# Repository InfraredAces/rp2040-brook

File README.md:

# rp2040-brook-form
An RP2040 powered board with the form factor of a Brook Universal Fightboard footprint

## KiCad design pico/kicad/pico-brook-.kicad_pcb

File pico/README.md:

The board is composed of Raspberry Pi Pico rather than an RP2040 stamp or an RP2040 with baremetal components. 

)

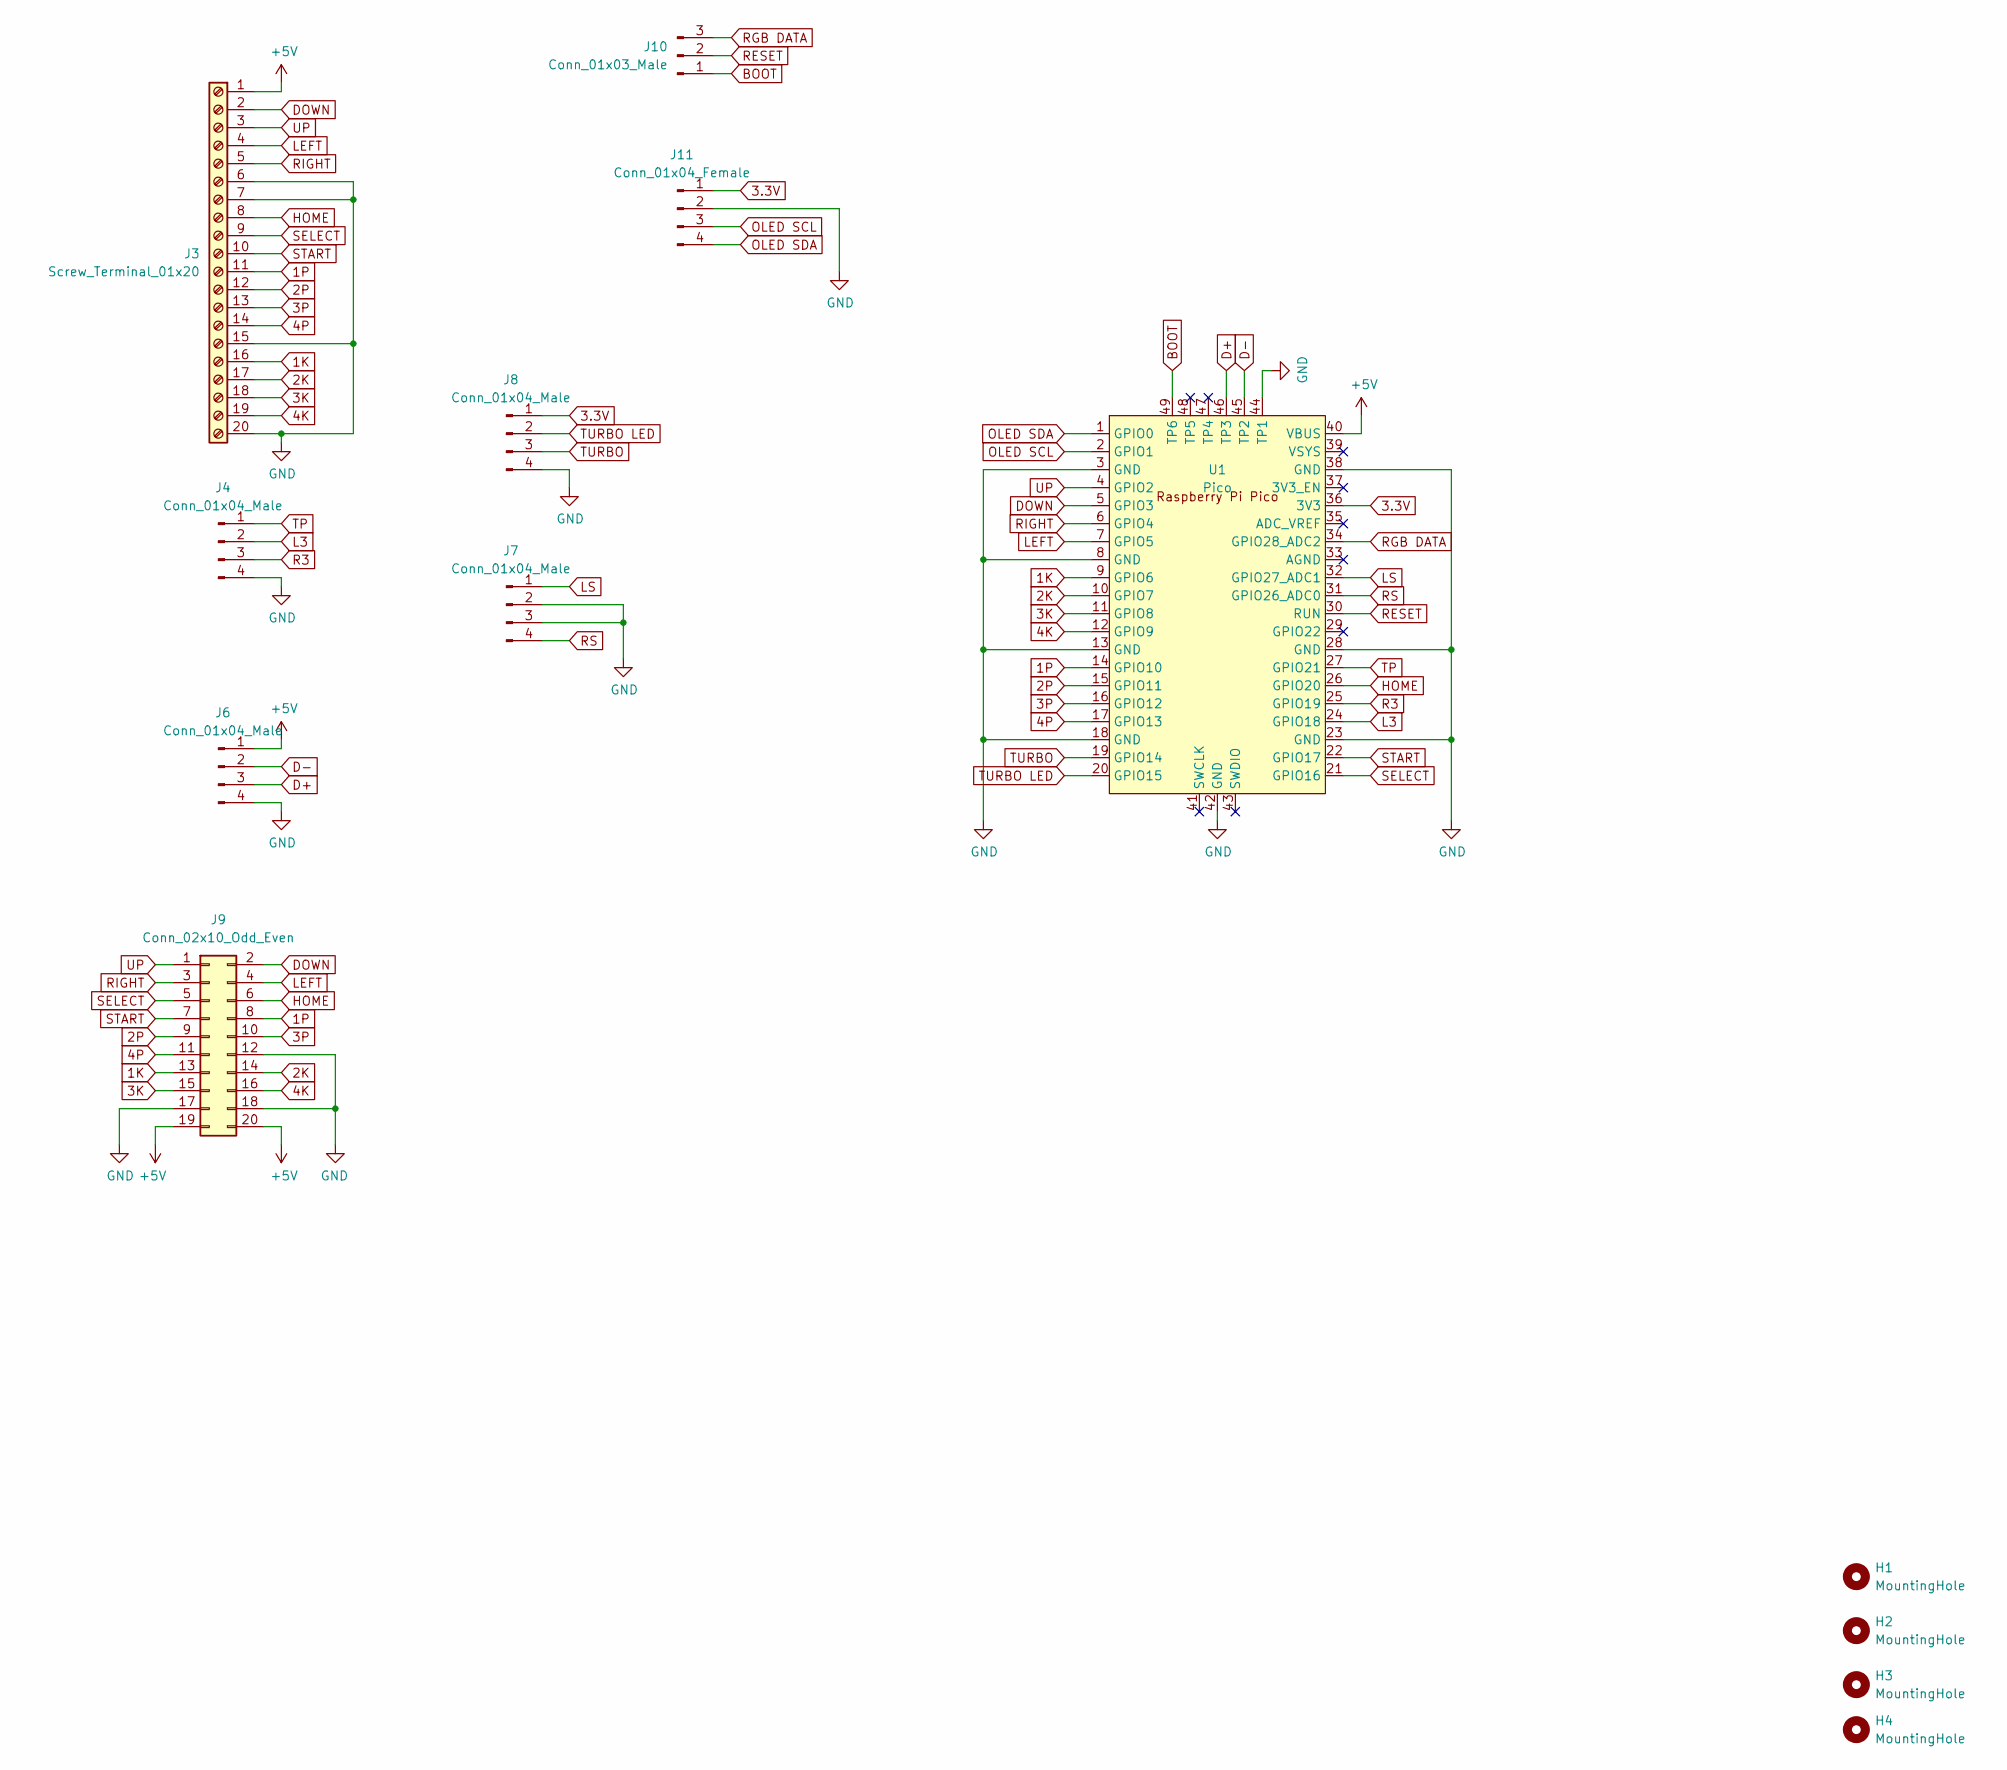
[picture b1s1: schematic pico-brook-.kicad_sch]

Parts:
H1, H2, H3, H4: MountingHole; MountingHole_3.2mm_M3
J3: Screw_Terminal_01x20; Wago_734-150_1x20_P3.50mm_Vertical
J4: Conn_01x04_Male; PinSocket_1x04_P2.00mm_Vertical
J6: Conn_01x04_Male; PinSocket_1x04_P2.54mm_Vertical
J7: Conn_01x04_Male; PinHeader_1x04_P2.54mm_Vertical
J8: Conn_01x04_Male; PinHeader_1x04_P2.00mm_Vertical
J9: Conn_02x10_Odd_Even; PinHeader_2x10_P2.54mm_Vertical
J10: Conn_01x03_Male; PinHeader_1x03_P2.54mm_Vertical
J11: Conn_01x04_Female; PinHeader_1x04_P2.54mm_Vertical
U1: Pico; RPi_Pico_SMD_TH

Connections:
1K: J3.16, J9.13, U1.9 (GPIO6)
1P: J3.11, J9.8, U1.14 (GPIO10)
2K: J3.17, J9.14, U1.10 (GPIO7)
2P: J3.12, J9.9, U1.15 (GPIO11)
3.3V: J8.1, J11.1, U1.36 (3V3)
3K: J3.18, J9.15, U1.11 (GPIO8)
3P: J3.13, J9.10, U1.16 (GPIO12)
4K: J3.19, J9.16, U1.12 (GPIO9)
4P: J3.14, J9.11, U1.17 (GPIO13)
+5V: J3.1, J6.1, J9.19, J9.20, U1.40 (VBUS)
BOOT: J10.1, U1.49 (TP6)
D+: J6.3, U1.46 (TP3)
D-: J6.2, U1.45 (TP2)
DOWN: J3.2, J9.2, U1.5 (GPIO3)
GND: J3.6, J3.7, J3.15, J3.20, J4.4, J6.4, J7.2, J7.3, J8.4, J9.12, J9.17, J9.18, J11.2, U1.3 (GND), U1.8 (GND), U1.13 (GND), U1.18 (GND), U1.23 (GND), U1.28 (GND), U1.38 (GND), U1.42 (GND), U1.44 (TP1)
HOME: J3.8, J9.6, U1.26 (GPIO20)
L3: J4.2, U1.24 (GPIO18)
LEFT: J3.4, J9.4, U1.7 (GPIO5)
LS: J7.1, U1.32 (GPIO27_ADC1)
OLED SCL: J11.3, U1.2 (GPIO1)
OLED SDA: J11.4, U1.1 (GPIO0)
R3: J4.3, U1.25 (GPIO19)
RESET: J10.2, U1.30 (RUN)
RGB DATA: J10.3, U1.34 (GPIO28_ADC2)
RIGHT: J3.5, J9.3, U1.6 (GPIO4)
RS: J7.4, U1.31 (GPIO26_ADC0)
SELECT: J3.9, J9.5, U1.21 (GPIO16)
START: J3.10, J9.7, U1.22 (GPIO17)
TP: J4.1, U1.27 (GPIO21)
TURBO: J8.3, U1.19 (GPIO14)
TURBO LED: J8.2, U1.20 (GPIO15)
UP: J3.3, J9.1, U1.4 (GPIO2)

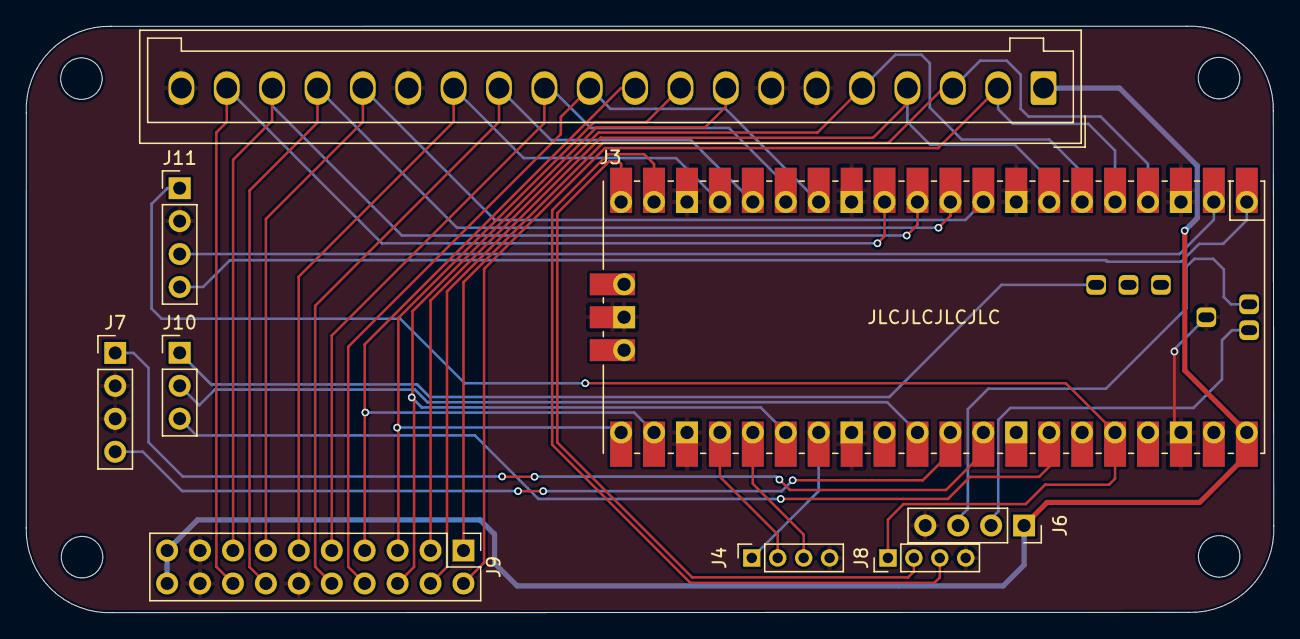
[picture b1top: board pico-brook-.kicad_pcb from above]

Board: 2 copper layers, 96.2 x 45.2 mm, 13 parts (0 on the bottom side), 32 nets.

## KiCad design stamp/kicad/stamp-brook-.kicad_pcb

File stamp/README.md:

The board is composed of an RP2040 stamp rather than a  Raspberry Pi Pico or an RP2040 with baremetal components. 

)

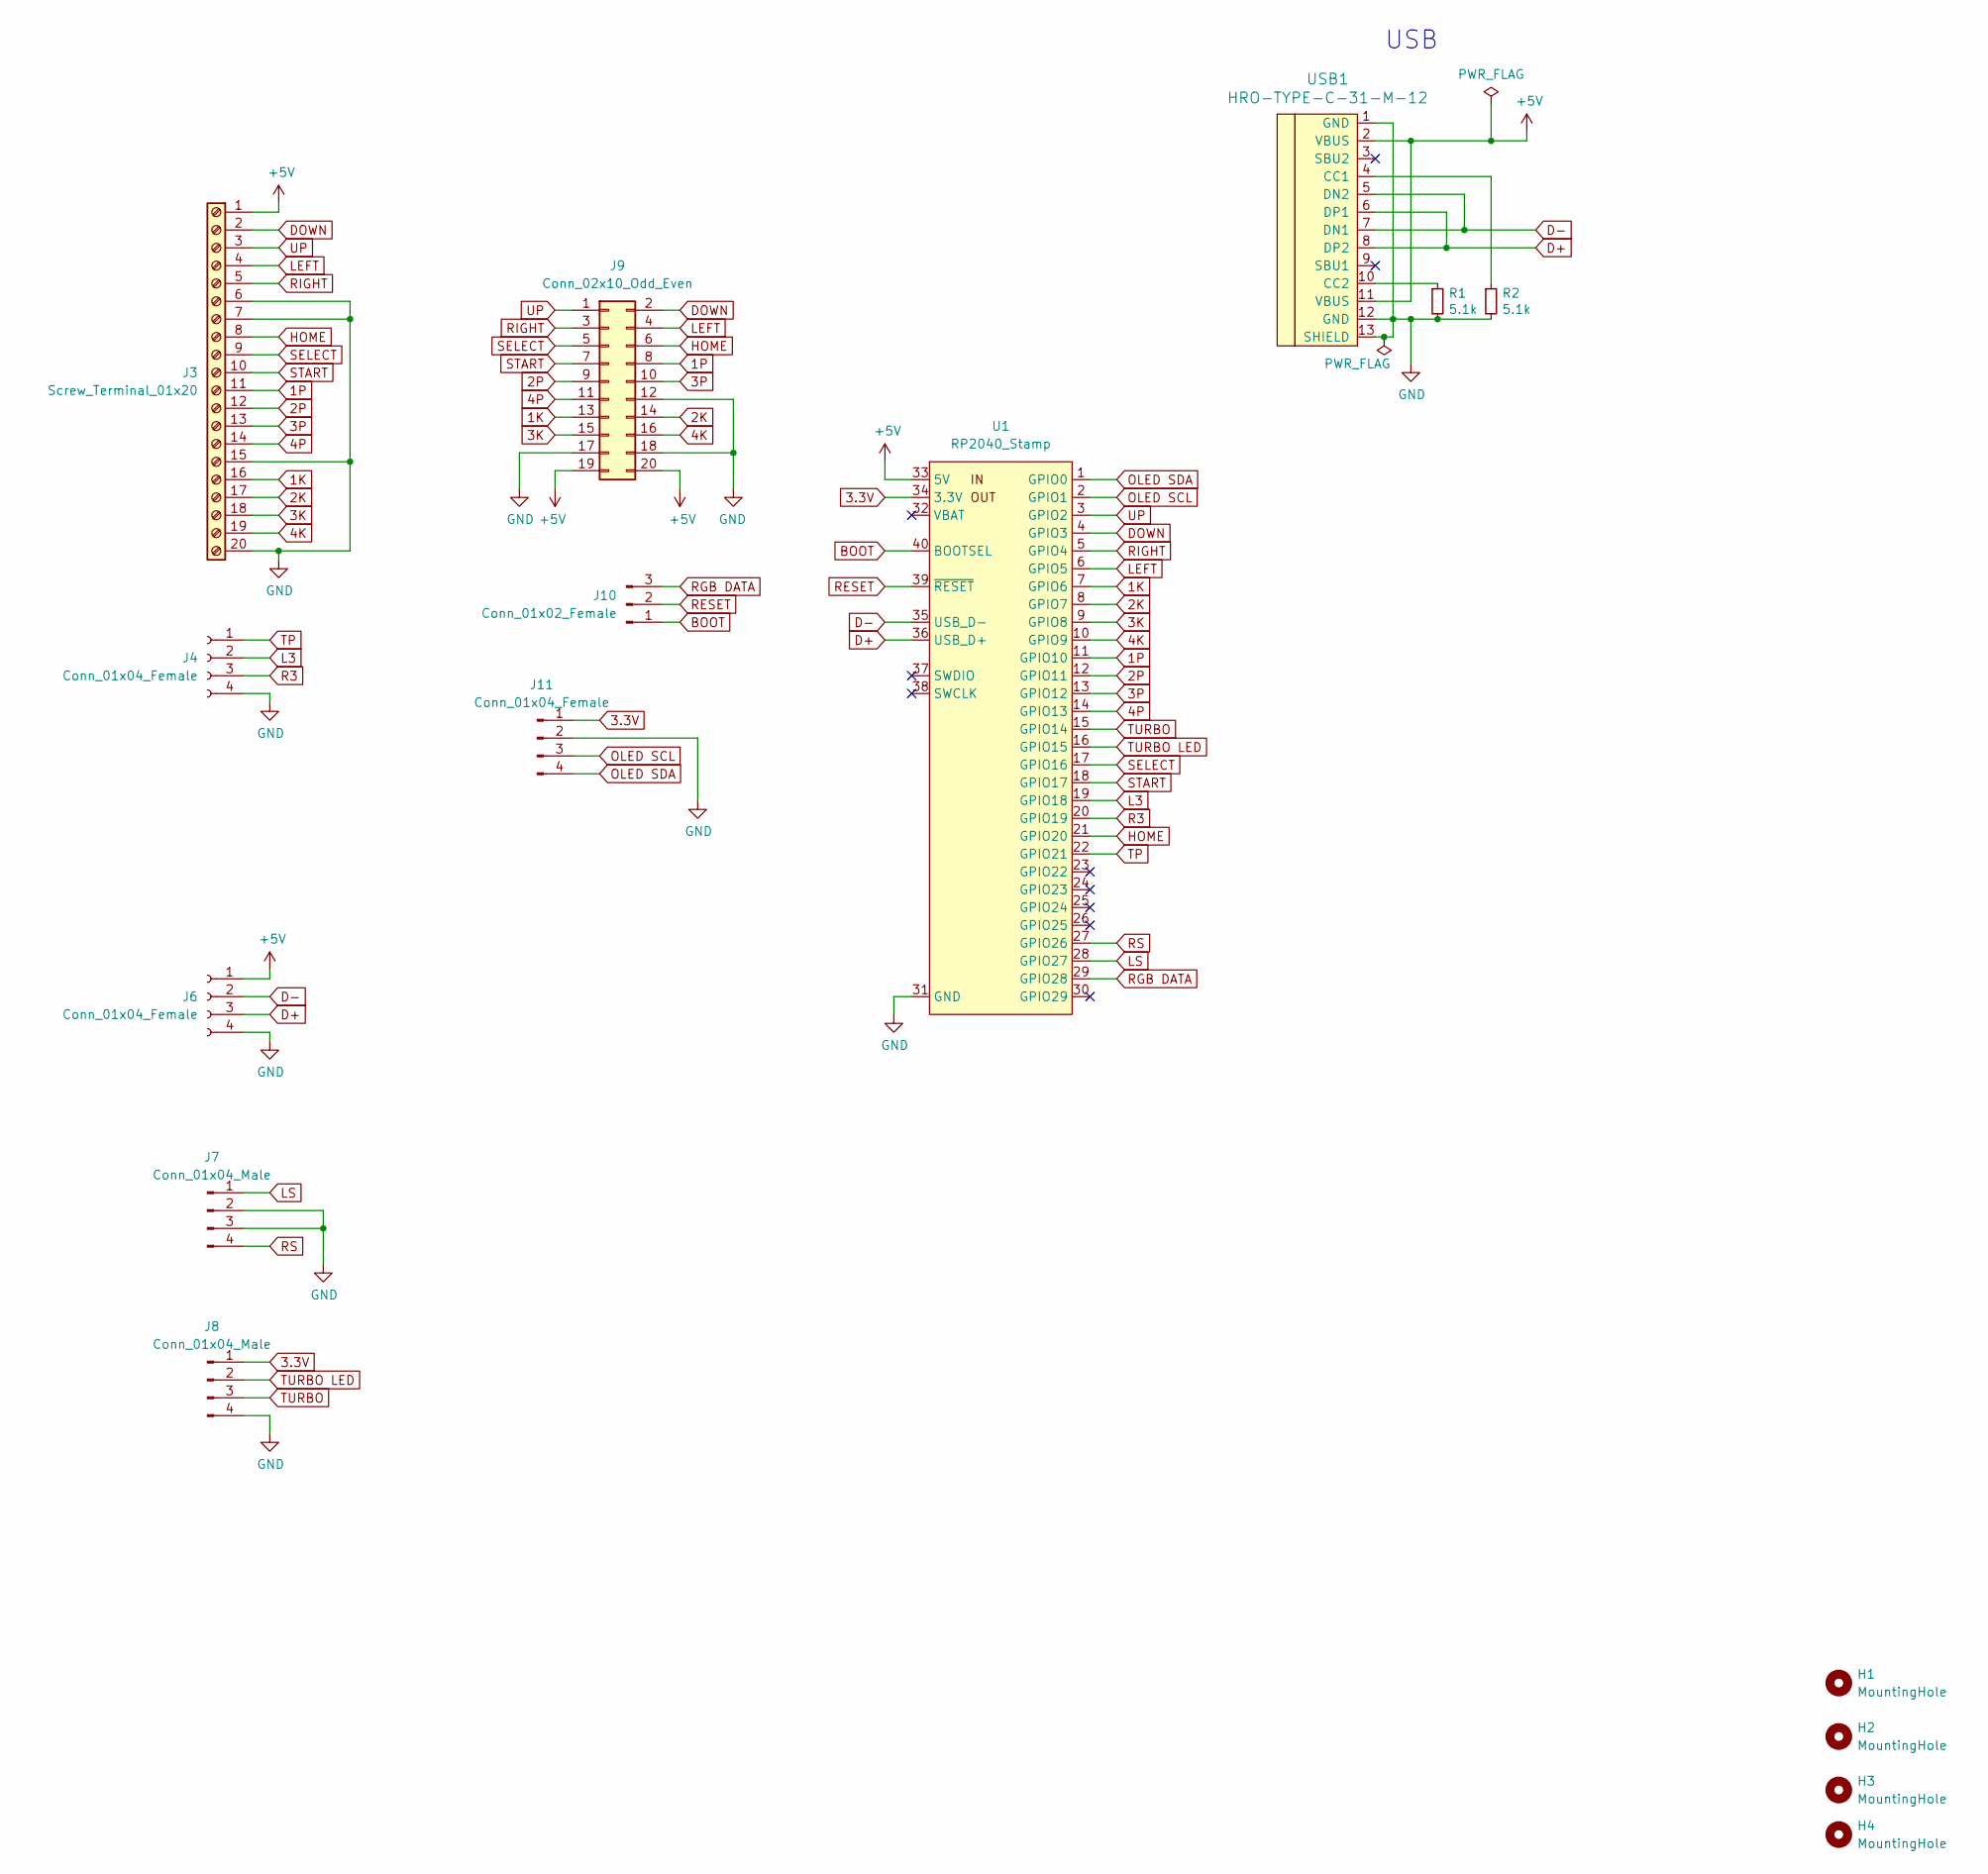
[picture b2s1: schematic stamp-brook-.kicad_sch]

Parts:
H1, H2, H3, H4: MountingHole; MountingHole_3.2mm_M3
J3: Screw_Terminal_01x20; Wago_734-150_1x20_P3.50mm_Vertical
J4: Conn_01x04_Female; PinSocket_1x04_P2.00mm_Vertical
J6: Conn_01x04_Female; PinSocket_1x04_P2.54mm_Vertical
J7: Conn_01x04_Male; PinHeader_1x04_P2.54mm_Vertical
J8: Conn_01x04_Male; PinHeader_1x04_P2.00mm_Vertical
J9: Conn_02x10_Odd_Even; PinSocket_2x10_P2.54mm_Vertical
J10: Conn_01x02_Female; PinHeader_1x03_P2.54mm_Vertical
J11: Conn_01x04_Female; PinHeader_1x04_P2.54mm_Vertical
R1, R2: 5.1k; RESC6332X70N; LCSC C25905
U1: RP2040_Stamp; RP2040_Stamp_SMD
USB1: HRO-TYPE-C-31-M-12; HRO-TYPE-C-31-M-12-Assembly; LCSC C165948

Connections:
1K: J3.16, J9.13, U1.7 (GPIO6)
1P: J3.11, J9.8, U1.11 (GPIO10)
2K: J3.17, J9.14, U1.8 (GPIO7)
2P: J3.12, J9.9, U1.12 (GPIO11)
3.3V: J8.1, J11.1, U1.34 (3.3V)
3K: J3.18, J9.15, U1.9 (GPIO8)
3P: J3.13, J9.10, U1.13 (GPIO12)
4K: J3.19, J9.16, U1.10 (GPIO9)
4P: J3.14, J9.11, U1.14 (GPIO13)
+5V: J3.1, J6.1, J9.19, J9.20, U1.33 (5V), USB1.2 (VBUS), USB1.11 (VBUS)
BOOT: J10.1, U1.40 (BOOTSEL)
D+: J6.3, U1.36 (USB_D+), USB1.6 (DP1), USB1.8 (DP2)
D-: J6.2, U1.35 (USB_D-), USB1.5 (DN2), USB1.7 (DN1)
DOWN: J3.2, J9.2, U1.4 (GPIO3)
GND: J3.6, J3.7, J3.15, J3.20, J4.4, J6.4, J7.2, J7.3, J8.4, J9.12, J9.17, J9.18, J11.2, R1.2, R2.2, U1.31 (GND), USB1.1 (GND), USB1.12 (GND), USB1.13 (SHIELD)
HOME: J3.8, J9.6, U1.21 (GPIO20)
L3: J4.2, U1.19 (GPIO18)
LEFT: J3.4, J9.4, U1.6 (GPIO5)
LS: J7.1, U1.28 (GPIO27)
unnamed: R1.1, USB1.10 (CC2)
unnamed: R2.1, USB1.4 (CC1)
OLED SCL: J11.3, U1.2 (GPIO1)
OLED SDA: J11.4, U1.1 (GPIO0)
R3: J4.3, U1.20 (GPIO19)
RESET: J10.2, U1.39 (~RESET)
RGB DATA: J10.3, U1.29 (GPIO28)
RIGHT: J3.5, J9.3, U1.5 (GPIO4)
RS: J7.4, U1.27 (GPIO26)
SELECT: J3.9, J9.5, U1.17 (GPIO16)
START: J3.10, J9.7, U1.18 (GPIO17)
TP: J4.1, U1.22 (GPIO21)
TURBO: J8.3, U1.15 (GPIO14)
TURBO LED: J8.2, U1.16 (GPIO15)
UP: J3.3, J9.1, U1.3 (GPIO2)

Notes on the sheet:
USB

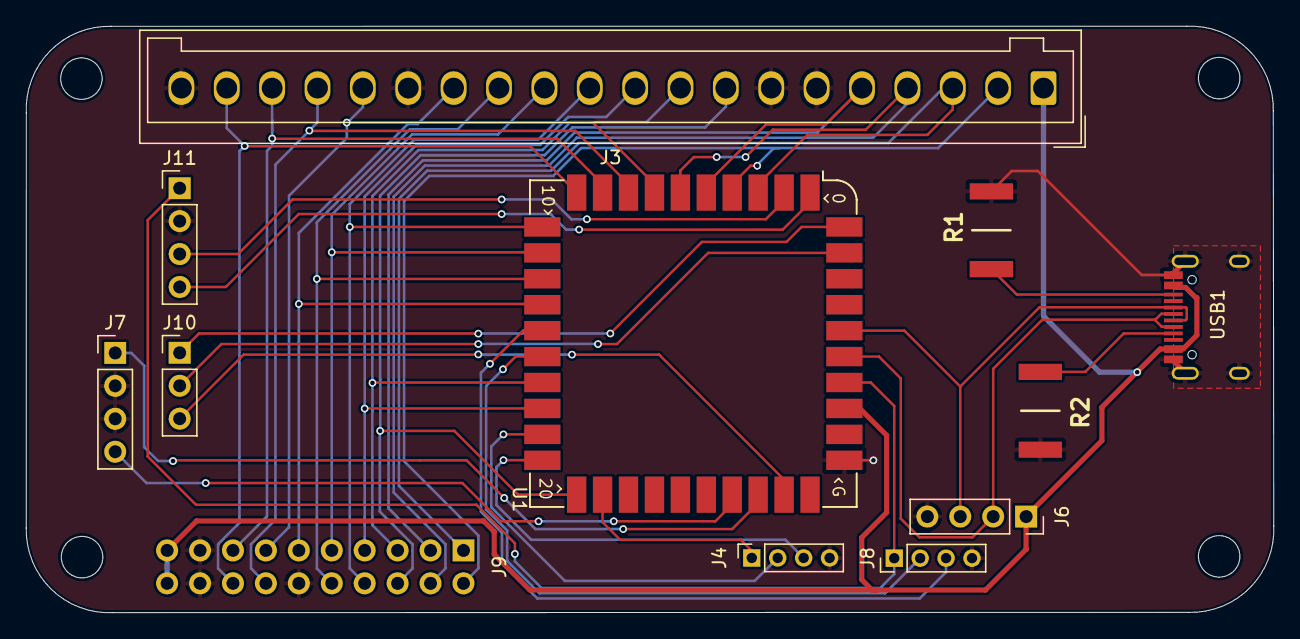
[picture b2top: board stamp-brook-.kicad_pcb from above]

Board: 2 copper layers, 96.2 x 45.2 mm, 16 parts (1 on the bottom side), 34 nets.

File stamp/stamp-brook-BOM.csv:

Comment,Designator,Footprint,LCSC
"MountingHole","H1,H2,H3,H4","MountingHole:MountingHole_3.2mm_M3",""
"Conn_01x02_Female","J10","Connector_PinHeader_2.54mm:PinHeader_1x03_P2.54mm_Vertical",""
"Conn_01x05_Male","J2,J5","Connector_PinHeader_2.00mm:PinHeader_1x05_P2.00mm_Vertical",""
"Screw_Terminal_01x20","J3","Connector_Wago:Wago_734-150_1x20_P3.50mm_Vertical",""
"Conn_01x04_Female","J4","Connector_PinSocket_2.00mm:PinSocket_1x04_P2.00mm_Vertical",""
"Conn_01x04_Female","J6","Connector_PinSocket_2.54mm:PinSocket_1x04_P2.54mm_Vertical",""
"Conn_01x04_Male","J7","Connector_PinHeader_2.54mm:PinHeader_1x04_P2.54mm_Vertical",""
"Conn_01x04_Male","J8","Connector_PinHeader_2.00mm:PinHeader_1x04_P2.00mm_Vertical",""
"Conn_02x10_Odd_Even","J9","Connector_PinSocket_2.54mm:PinSocket_2x10_P2.54mm_Vertical",""
"5.1k","R1,R2","Resistor_SMD:R_0402_1005Metric","C25905"
"RP2040_Stamp","U1","RP2040_Stamp:RP2040_Stamp_SMD",""
"HRO-TYPE-C-31-M-12","USB1","Type-C:HRO-TYPE-C-31-M-12-Assembly","C165948"

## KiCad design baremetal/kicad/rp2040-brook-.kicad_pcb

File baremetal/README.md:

The board is composed of an RP2040 with baremetal components rather than an RP2040 stamp or Raspberry Pi Pico.

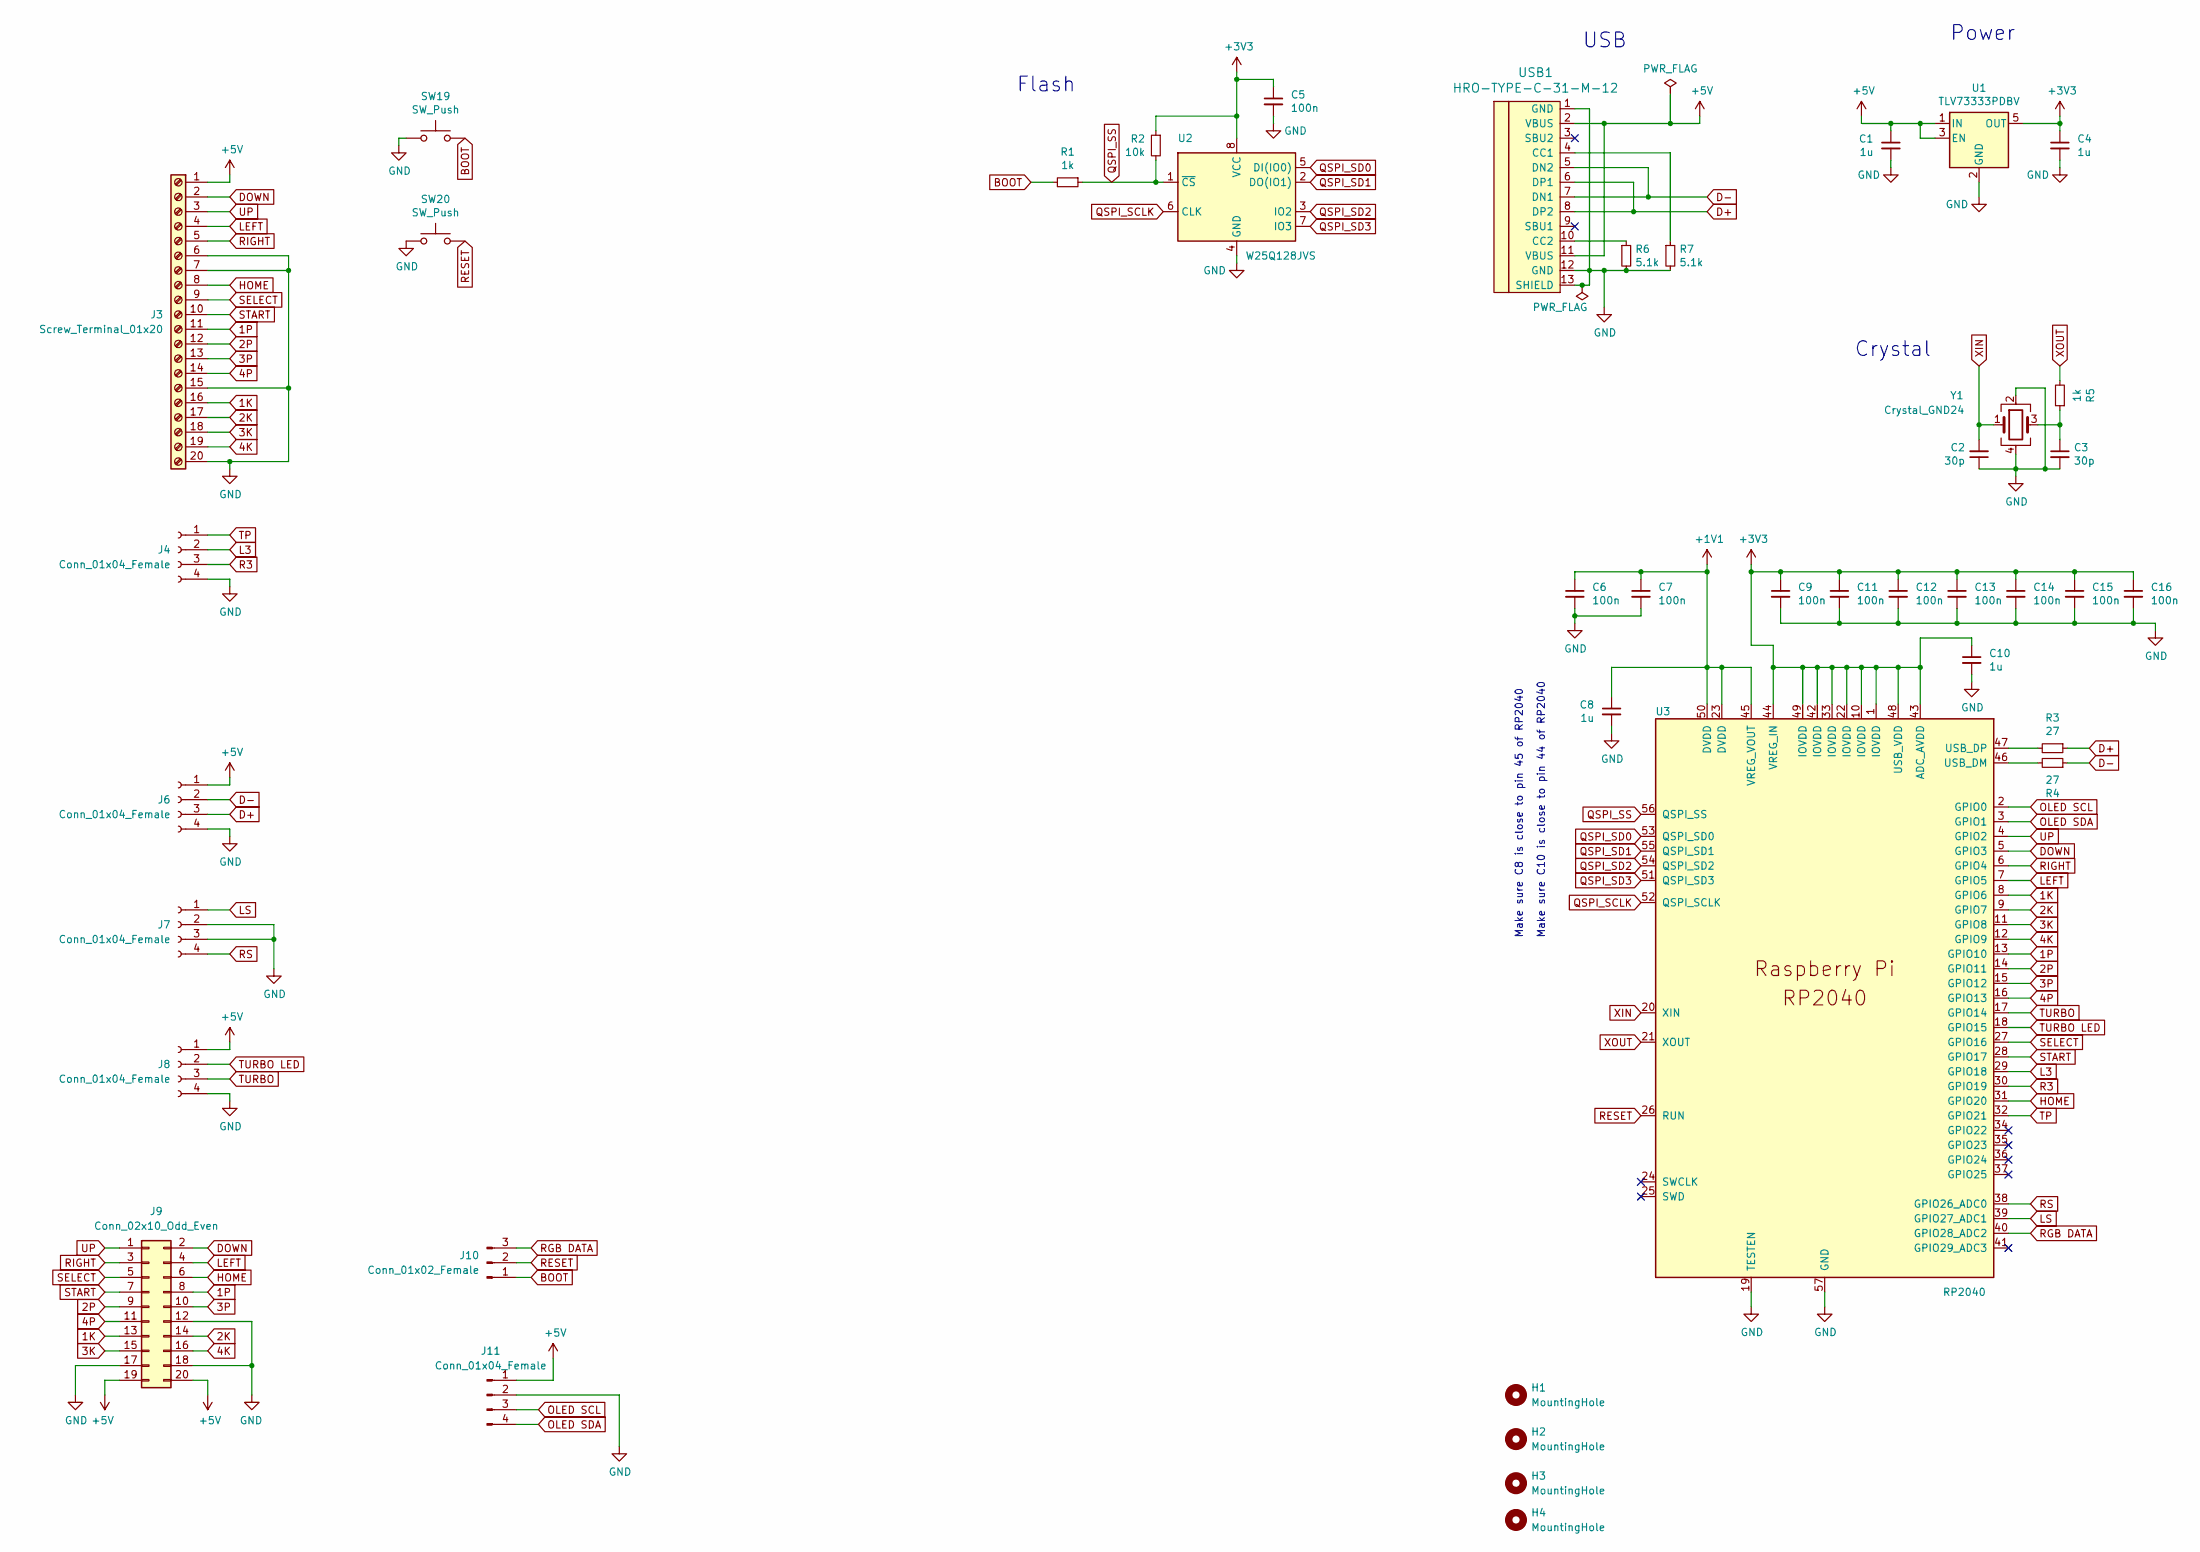
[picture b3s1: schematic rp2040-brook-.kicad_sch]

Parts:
C1, C4, C8, C10: 1u; C_0402_1005Metric; LCSC C52923
C2, C3: 30p; C_0402_1005Metric; LCSC C1570
C5, C6, C7, C9, C11, C12, C13, C14, C15, C16: 100n; C_0402_1005Metric; LCSC C1525
H1, H2, H3, H4: MountingHole; MountingHole_3.2mm_M3
J3: Screw_Terminal_01x20; Wago_734-150_1x20_P3.50mm_Vertical
J4, J8: Conn_01x04_Female; PinSocket_1x04_P2.00mm_Vertical
J6, J7: Conn_01x04_Female; PinSocket_1x04_P2.54mm_Vertical
J9: Conn_02x10_Odd_Even; PinSocket_2x10_P2.54mm_Vertical
J10: Conn_01x02_Female; PinHeader_1x03_P2.54mm_Vertical
J11: Conn_01x04_Female; PinHeader_1x04_P2.54mm_Vertical
R1, R5: 1k; R_0402_1005Metric; LCSC C11702
R2: 10k; R_0402_1005Metric; LCSC C25744
R3, R4: 27; R_0402_1005Metric; LCSC C138021
R6, R7: 5.1k; R_0402_1005Metric; LCSC C25905
SW19, SW20: SW_Push; SW_SPST_Omron_B3FS-100xP; LCSC C271750
U1: TLV73333PDBV; SOT-23-5; LCSC C134139
U2: W25Q128JVS; SOIC-8_5.23x5.23mm_P1.27mm; LCSC C97521
U3: RP2040; RP2040-QFN-56; LCSC C2040
USB1: HRO-TYPE-C-31-M-12; HRO-TYPE-C-31-M-12-Assembly; LCSC C165948
Y1: Crystal_GND24; Crystal_SMD_3225-4Pin_3.2x2.5mm; LCSC C9002

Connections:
1K: J3.16, J9.13, U3.8 (GPIO6)
1P: J3.11, J9.8, U3.13 (GPIO10)
2K: J3.17, J9.14, U3.9 (GPIO7)
2P: J3.12, J9.9, U3.14 (GPIO11)
3K: J3.18, J9.15, U3.11 (GPIO8)
3P: J3.13, J9.10, U3.15 (GPIO12)
4K: J3.19, J9.16, U3.12 (GPIO9)
4P: J3.14, J9.11, U3.16 (GPIO13)
+1V1: C6.1, C7.1, C8.1, U3.23 (DVDD), U3.45 (VREG_VOUT), U3.50 (DVDD)
+3V3: C4.1, C5.1, C9.1, C10.1, C11.1, C12.1, C13.1, C14.1, C15.1, C16.1, R2.1, U1.5 (OUT), U2.8 (VCC), U3.1 (IOVDD), U3.10 (IOVDD), U3.22 (IOVDD), U3.33 (IOVDD), U3.42 (IOVDD), U3.43 (ADC_AVDD), U3.44 (VREG_IN), U3.48 (USB_VDD), U3.49 (IOVDD)
+5V: C1.1, J3.1, J6.1, J8.1, J9.19, J9.20, J11.1, U1.1 (IN), U1.3 (EN), USB1.2 (VBUS), USB1.11 (VBUS)
BOOT: J10.1, R1.2, SW19.2
D+: J6.3, R3.1, USB1.6 (DP1), USB1.8 (DP2)
D-: J6.2, R4.1, USB1.5 (DN2), USB1.7 (DN1)
DOWN: J3.2, J9.2, U3.5 (GPIO3)
GND: C1.2, C2.1, C3.2, C4.2, C5.2, C6.2, C7.2, C8.2, C9.2, C10.2, C11.2, C12.2, C13.2, C14.2, C15.2, C16.2, J3.6, J3.7, J3.15, J3.20, J4.4, J6.4, J7.2, J7.3, J8.4, J9.12, J9.17, J9.18, J11.2, R6.2, R7.2, SW19.1, SW20.1, U1.2 (GND), U2.4 (GND), U3.19 (TESTEN), U3.57 (GND), USB1.1 (GND), USB1.12 (GND), USB1.13 (SHIELD), Y1.2, Y1.4
HOME: J3.8, J9.6, U3.31 (GPIO20)
L3: J4.2, U3.29 (GPIO18)
LEFT: J3.4, J9.4, U3.7 (GPIO5)
LS: J7.1, U3.39 (GPIO27_ADC1)
unnamed: C3.1, R5.1, Y1.3
unnamed: R3.2, U3.47 (USB_DP)
unnamed: R4.2, U3.46 (USB_DM)
unnamed: R6.1, USB1.10 (CC2)
unnamed: R7.1, USB1.4 (CC1)
OLED SCL: J11.3, U3.2 (GPIO0)
OLED SDA: J11.4, U3.3 (GPIO1)
QSPI_SCLK: U2.6 (CLK), U3.52 (QSPI_SCLK)
QSPI_SD0: U2.5 (DI(IO0)), U3.53 (QSPI_SD0)
QSPI_SD1: U2.2 (DO(IO1)), U3.55 (QSPI_SD1)
QSPI_SD2: U2.3 (IO2), U3.54 (QSPI_SD2)
QSPI_SD3: U2.7 (IO3), U3.51 (QSPI_SD3)
QSPI_SS: R1.1, R2.2, U2.1 (~CS), U3.56 (QSPI_SS)
R3: J4.3, U3.30 (GPIO19)
RESET: J10.2, SW20.2, U3.26 (RUN)
RGB DATA: J10.3, U3.40 (GPIO28_ADC2)
RIGHT: J3.5, J9.3, U3.6 (GPIO4)
RS: J7.4, U3.38 (GPIO26_ADC0)
SELECT: J3.9, J9.5, U3.27 (GPIO16)
START: J3.10, J9.7, U3.28 (GPIO17)
TP: J4.1, U3.32 (GPIO21)
TURBO: J8.3, U3.17 (GPIO14)
TURBO LED: J8.2, U3.18 (GPIO15)
UP: J3.3, J9.1, U3.4 (GPIO2)
XIN: C2.2, U3.20 (XIN), Y1.1
XOUT: R5.2, U3.21 (XOUT)

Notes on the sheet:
Make sure C8 is close to pin 45 of RP2040
Make sure C10 is close to pin 44 of RP2040
Power
USB
Flash
Crystal

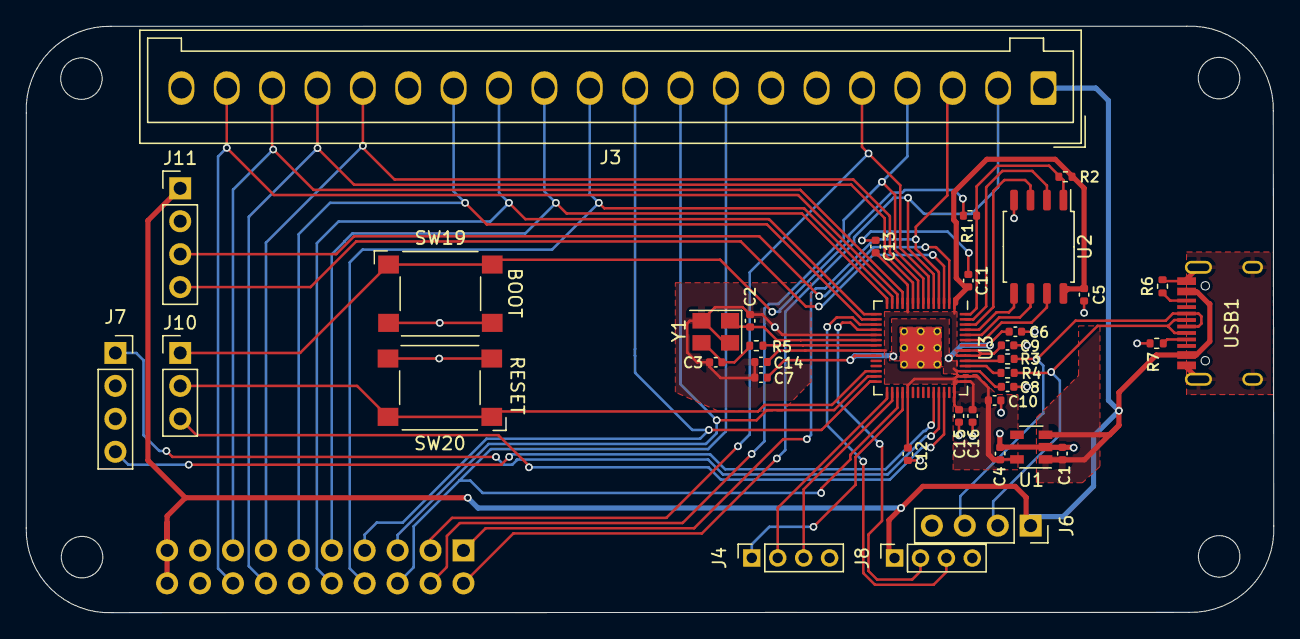
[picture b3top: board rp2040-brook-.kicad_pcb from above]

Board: 2 copper layers, 96.2 x 45.2 mm, 42 parts (1 on the bottom side), 46 nets.

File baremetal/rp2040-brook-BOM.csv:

Comment,Designator,Footprint,LCSC
"1u","C1,C4,C8,C10","Capacitor_SMD:C_0402_1005Metric","C52923"
"30p","C2,C3","Capacitor_SMD:C_0402_1005Metric","C1570"
"100n","C5,C6,C7,C9,C11,C12,C13,C14,C15,C16","Capacitor_SMD:C_0402_1005Metric","C1525"
"MountingHole","H1,H2,H3,H4","MountingHole:MountingHole_3.2mm_M3",""
"Conn_01x02_Female","J1","Connector_PinHeader_2.54mm:PinHeader_1x03_P2.54mm_Vertical",""
"Conn_01x05_Female","J2,J5","Connector_PinSocket_2.00mm:PinSocket_1x05_P2.00mm_Vertical",""
"Screw_Terminal_01x20","J3","Connector_Wago:Wago_734-150_1x20_P3.50mm_Vertical",""
"Conn_01x04_Female","J4,J8","Connector_PinSocket_2.00mm:PinSocket_1x04_P2.00mm_Vertical",""
"Conn_01x04_Female","J6,J7","Connector_PinSocket_2.54mm:PinSocket_1x04_P2.54mm_Vertical",""
"Conn_02x10_Odd_Even","J9","Connector_PinSocket_2.54mm:PinSocket_2x10_P2.54mm_Vertical",""
"1k","R1,R5","Resistor_SMD:R_0402_1005Metric","C11702"
"10k","R2","Resistor_SMD:R_0402_1005Metric","C25744"
"27","R3,R4","Resistor_SMD:R_0402_1005Metric","C138021"
"5.1k","R6,R7","Resistor_SMD:R_0402_1005Metric","C25905"
"SW_Push","SW19,SW20","Button_Switch_SMD:SW_SPST_Omron_B3FS-100xP","C271750"
"TLV73333PDBV","U1","Package_TO_SOT_SMD:SOT-23-5","C134139"
"W25Q128JVS","U2","Package_SO:SOIC-8_5.23x5.23mm_P1.27mm","C97521"
"RP2040","U3","RP2040:RP2040-QFN-56","C2040"
"HRO-TYPE-C-31-M-12","USB1","Type-C:HRO-TYPE-C-31-M-12-Assembly","C165948"
"Crystal_GND24","Y1","Crystal:Crystal_SMD_3225-4Pin_3.2x2.5mm","C9002"

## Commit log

2022-07-30 Add Pico based board
2022-07-30 Move README to root
2022-07-30 Add README to versions and add images to assets
2022-07-30 Update gerber, BOM, and CPL files for all versions
2022-07-31 Add SOCD pin holes, and update PCB footprint and symbol
2022-07-31 Add required symbols and footprints for various boards
2022-07-31 Update baremetal gerber, BOM, and CPL files
2022-07-31 Update pico gerber, BOM, and CPL files
2022-07-31 Add RP2040 stamp based kicad, gerber, BOM, and CPL files
2022-07-31 Update RP2040-Brook Footprint and Symbol
2022-08-18 Add turbo and oled pins and traces
2022-08-18 Swap OLED SDA and OLED SCL pins and headers on PCB and Schematic
2022-08-20 Add Turbo pins, OLED pins, and LS/DP/RS pins. Change Resistors to larger component
2022-08-20 Misc changes
2022-08-20 Add CRCW25125K10JNTG, large resistor footprint
2022-08-20 Remove Baremetal Board
2022-08-23 Re-add baremetal board, reorganise components, add OLED and TURBO pins
2022-08-23 Minor adjustments to traces, remove J2 and J5 due to nonuse
2022-08-25 Update Pico Board
